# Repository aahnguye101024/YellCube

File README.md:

# YellCube
This device is intended to connect stream audio and flash lights representative of the audio. This device streams songs that are uploaded to another repo (https://github.com/aahnguye101024/ESP32Audio). This project was also a way for me to test out the 3D printer I just bought in a fun way. With an ESP32 pico d4 with an antenna, onboard leds, a dedicated SK6812 LED board, an audio amplifier, an onboard lipo with supported charging and uploading straight to the pico D4, this board can be easily programmed and adapted to any of your speaker and lights project needs.

# Main Board

# Lights Board

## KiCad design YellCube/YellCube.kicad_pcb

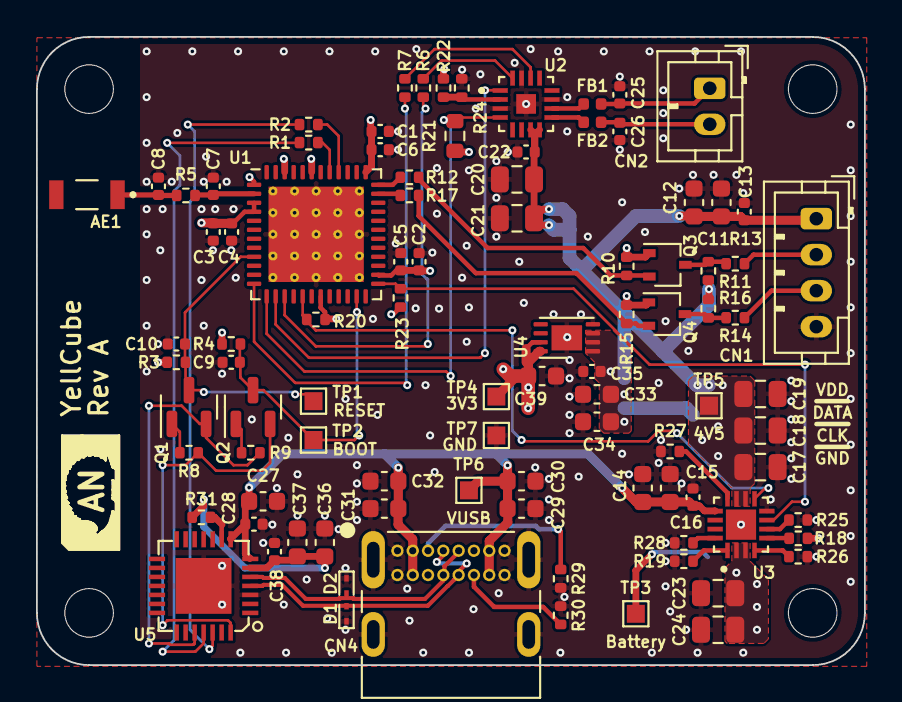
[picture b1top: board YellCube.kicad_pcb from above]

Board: 4 copper layers, 46.0 x 34.9 mm, 99 parts (1 on the bottom side), 50 nets.

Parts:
AE1: AMCA31-2R450G-S1F-T3; ANT_AMCA31-2R450G-S1F-T3
C1, C2, C3, C10: 1uF; C_0402_1005Metric
C4, C5, C6, C9, C13, C16, C22, C28, C35, C38: 0.1uF; C_0402_1005Metric
C7: 2.7pF; C_0402_1005Metric
C8: 2pF; C_0402_1005Metric
C11, C12, C33, C34, C39: 4.7uF; C_0603_1608Metric
C14, C15, C27, C29, C30, C31, C32, C36, C37: 2.2uF; C_0603_1608Metric
C17, C18, C19, C20, C21, C23, C24: 10uF; C_0805_2012Metric
C25, C26: 220pF; C_0402_1005Metric
CN1: B4B-PH-K-S(LF)(SN); JST_PH_B4B-PH-K_1x04_P2.00mm_Vertical
CN2: B2B-PH-K-S(LF)(SN); JST_PH_B2B-PH-K_1x02_P2.00mm_Vertical
CN3: S2B-PH-SM4-TB(LF)(SN); JST_S2B-PH-SM4-TB(LF)(SN)
CN4: 2137160001
D1, D2: ESD7951ST5G; D_SOD-923
FB1, FB2: BLM15PX601SN1D; L_0402_1005Metric
H1, H2, H3, H4: MountingHole; MountingHole_2.7mm_M2.5_ISO14580
Q1, Q2: MMBT3904; SOT-23
Q3, Q4: BSS138W-7-F; SOT-323_SC-70
R1, R2, R5, R12, R13, R14, R17: 0; R_0402_1005Metric
R3, R8, R9, R10, R11, R15, R16, R18, R19, R20, R23, R25, R26, R31: 10k; R_0402_1005Metric
R4, R28: 4.7k; R_0402_1005Metric
R6, R7: 33; R_0402_1005Metric
R21: 680k; R_0603_1608Metric
R22, R24: 100k; R_0402_1005Metric
R27: 3.09k; R_0402_1005Metric
R29, R30: 5.1k; R_0402_1005Metric
TP1: RESET; CurrentTestPoint
TP2: BOOT; CurrentTestPoint
TP3: Battery; CurrentTestPoint
TP4: 3V3; CurrentTestPoint
TP5: 4V5; CurrentTestPoint
TP6: VUSB; CurrentTestPoint
TP7: GND; CurrentTestPoint
U1: ESP32-PICO-D4; QFN-48-1EP_7x7mm_P0.5mm_EP5.3x5.3mm_ThermalVias
U2: MAX98357AETE+T; QFN50P300X300X80-17N
U3: BQ24232HARGTR; QFN50P300X300X100-17N
U4: MCP1725T-3302E/MC; MCP1725T-3302E
U5: CP2102-GMR; QFN28G_0.5-5X5MM

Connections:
+3V3: C1.1, C2.1, C3.1, C4.1, C5.1, C6.1, C39.1, Q3.1 (G), Q4.1 (G), R3.1, R4.1, R10.1, R15.1, R18.1, R20.2, R21.1, R22.2, R23.2, TP4.1, U1.1 (VDDA), U1.3 (VDDA3P3), U1.4 (VDDA3P3), U1.19 (VDD3P3_RTC), U1.26 (VDD_SDIO), U1.37 (VDD3P3_CPU), U1.43 (VDDA), U1.46 (VDDA), U4.7 (SENSE), U4.8 (VOUT)
+BATT: C23.1, C24.1, CN3.2, TP3.1, U3.2 (BAT), U3.3 (BAT)
/AUDIO_BCLK: R6.2, U2.16 (BCLK)
/AUDIO_DIN: U1.14 (IO25), U2.1 (DIN)
/AUDIO_LRCLK: R7.2, U2.14 (LRCLK)
/AUDIO_OUTN: C25.1, CN2.1, FB1.2
/AUDIO_OUTP: C26.1, CN2.2, FB2.2
/AUDIO_SD: R21.2, U1.13 (IO33), U2.4 (~SD_MODE)
/DTR: Q2.2 (E), R8.2, U5.28 (DTR)
/ESP_EN: C10.1, Q1.3 (C), R3.2, TP1.1, U1.9 (EN)
/IO0: C9.1, Q2.3 (C), R4.2, TP2.1, U1.23 (IO0)
/LED_CLK: R17.1, U1.35 (IO18)
/LED_CON_CLK: CN1.3, R14.2
/LED_CON_DATA: CN1.2, R13.2
/LED_DATA: R12.1, U1.36 (IO23)
/LNA_IN: C7.1, R5.2, U1.2 (LNA_IN)
/LNA_OUT: AE1.1 (A), C8.1, R5.1
/RTS: Q1.2 (E), R9.2, U5.24 (RTS)
/UART_RX: R1.1, U5.25 (RXD)
/UART_TX: R2.1, U5.26 (TXD)
/USB_N: CN4.A7 (D-), CN4.B7 (D-), D2.2 (A2), U5.5 (D-)
/USB_P: CN4.A6 (D+), CN4.B6 (D+), D1.2 (A2), U5.4 (D+)
/nCHG: R20.1, U1.17 (IO14), U3.9 (~CHG)
/nPGOOD: R23.1, U1.25 (IO16), U3.7 (~PGOOD)
GND: C1.2, C2.2, C3.2, C4.2, C5.2, C6.2, C7.2, C8.2, C9.2, C10.2, C11.2, C12.2, C13.2, C14.2, C15.2, C16.2, C17.2, C18.2, C19.2, C20.2, C21.2, C22.2, C23.2, C24.2, C25.2, C26.2, C27.2, C28.2, C29.2, C30.2, C31.2, C32.2, C33.2, C34.2, C35.2, C36.2, C37.2, C38.2, C39.2, CN1.4, CN3.1, CN3.MP (MountPin), CN4.A1 (GND), CN4.A12 (GND), CN4.B1 (GND), CN4.B12 (GND), CN4.S (SHIELD), D1.1 (A1), D2.1 (A1), R19.2, R24.1, R25.2, R26.2, R27.2, R28.2, R29.2, R30.2, TP7.1, U1.49 (GND), U2.3 (GND), U2.11 (GND), U2.15 (GND), U2.17 (EP), U3.8 (VSS), U3.17 (THERMALPAD), U4.4 (GND), U4.9 (PAD), U5.3 (GND), U5.29 (GND)
unnamed: C36.1, C37.1, C38.1, R31.1, U5.6 (VDD)
unnamed: CN4.A5 (CC1), R29.1
unnamed: CN4.B5 (CC2), R30.1
unnamed: FB1.1, U2.10 (OUTN)
unnamed: FB2.1, U2.9 (OUTP)
unnamed: Q1.1 (B), R8.1
unnamed: Q2.1 (B), R9.1
unnamed: Q3.2 (S), R10.2, R12.2
unnamed: Q3.3 (D), R11.2, R13.1
unnamed: Q4.2 (S), R15.2, R17.2
unnamed: Q4.3 (D), R14.1, R16.2
unnamed: R1.2, U1.41 (U0TXD)
unnamed: R2.2, U1.40 (U0RXD)
unnamed: R6.1, U1.15 (IO26)
unnamed: R7.1, U1.12 (IO32)
unnamed: R18.2, U3.5 (EN2)
unnamed: R19.1, U3.1 (TS)
unnamed: R22.1, R24.2, U2.2 (GAIN_SLOT)
unnamed: R25.1, U3.6 (EN1)
unnamed: R26.1, U3.4 (~CE)
unnamed: R27.1, U3.12 (ILIM)
unnamed: R28.1, U3.16 (ISET)
unnamed: R31.2, U5.9 (~RST)
VBUS: C14.1, C15.1, C16.1, C27.1, C28.1, C29.1, C30.1, C31.1, C32.1, CN4.A4 (VBUS), CN4.A9 (VBUS), CN4.B4 (VBUS), CN4.B9 (VBUS), TP6.1, U3.13 (IN), U5.7 (REGIN), U5.8 (VBUS)
VDD: C11.1, C12.1, C13.1, C17.1, C18.1, C19.1, C20.1, C21.1, C22.1, C33.1, C34.1, C35.1, CN1.1, R11.1, R16.1, TP5.1, U2.7 (VDD), U2.8 (VDD), U3.10 (OUT), U3.11 (OUT), U4.1 (VIN), U4.2 (VIN), U4.3 (~SHDN)

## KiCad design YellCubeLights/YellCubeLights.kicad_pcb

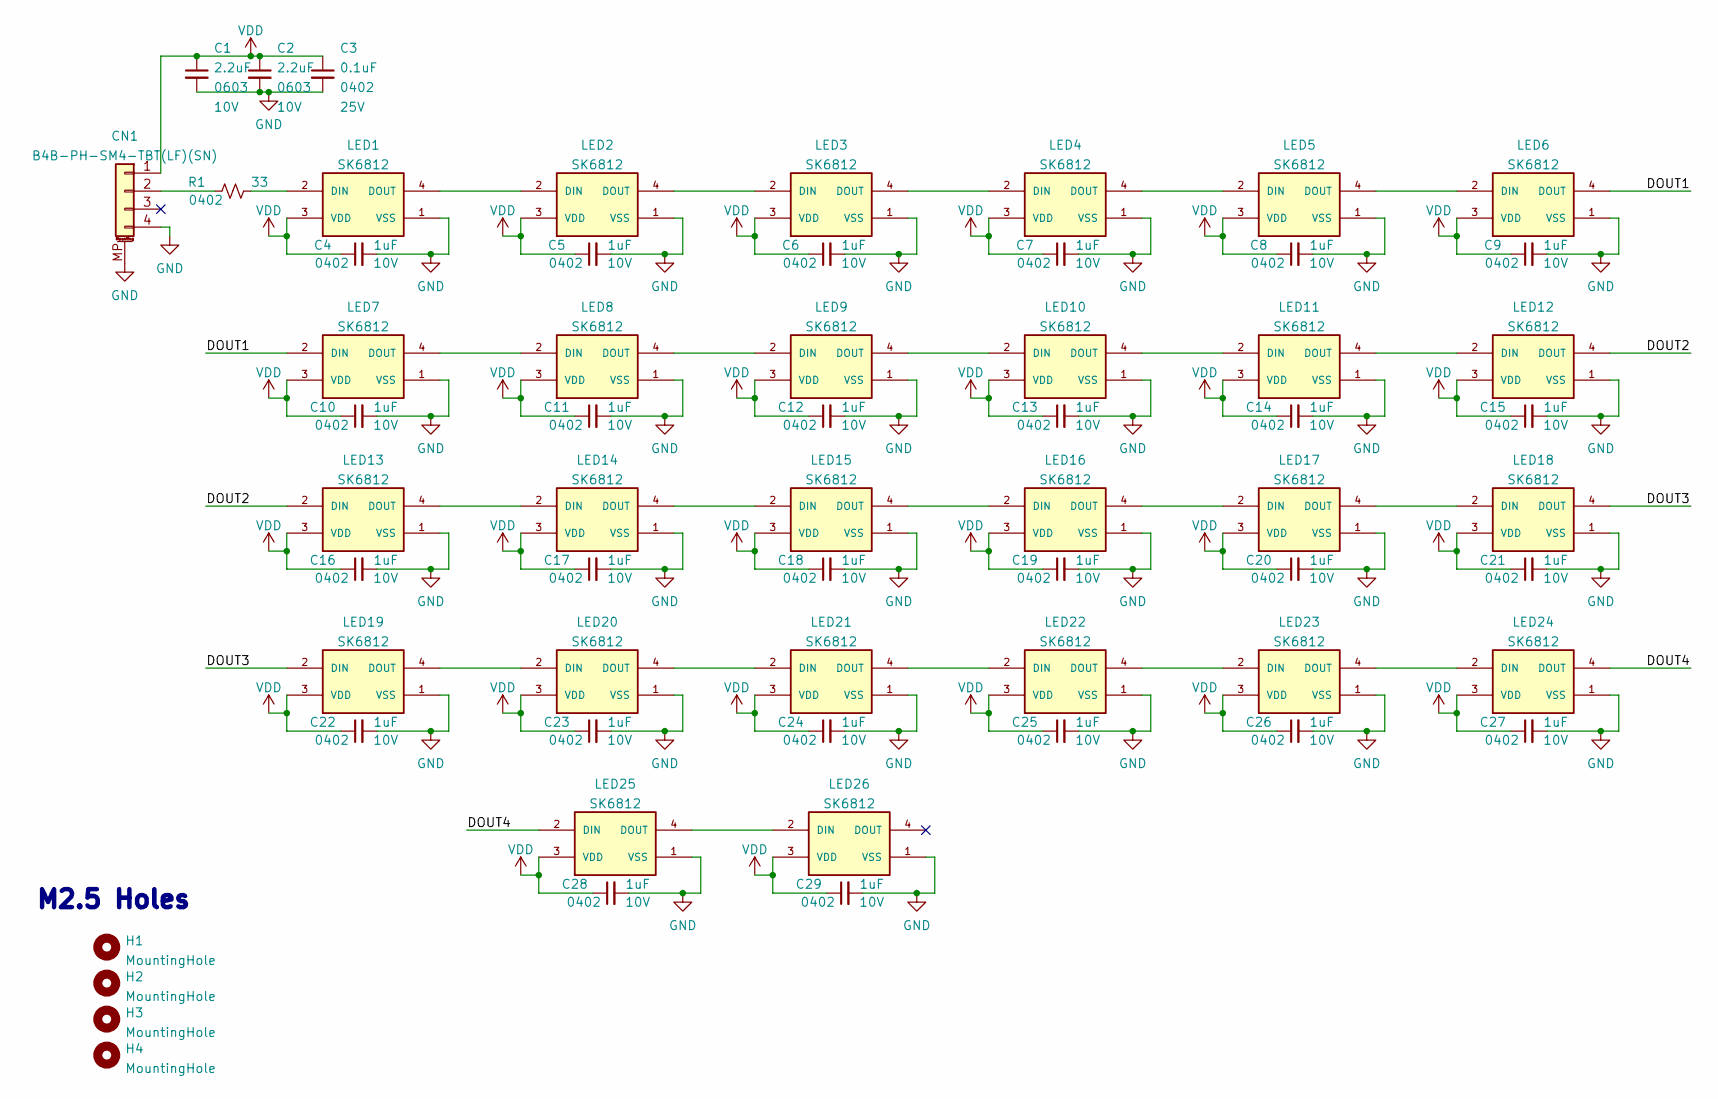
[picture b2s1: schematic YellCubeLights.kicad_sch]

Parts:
C1, C2: 2.2uF; C_0603_1608Metric; Voltage 10V; Part Number 1276-1085-1-ND
C3: 0.1uF; C_0402_1005Metric; Voltage 25V; Part Number 1276-1043-1-ND
C4, C5, C6, C7, C8, C9, C10, C11, C12, C13, C14, C15, C16, C17, C18, C19, C20, C21, C22, C23, C24, C25, C26, C27, C28, C29: 1uF; C_0402_1005Metric; Voltage 10V; Part Number 1276-1076-1-ND
CN1: B4B-PH-SM4-TBT(LF)(SN); Part Number 455-2873-1-ND
H1, H2, H3, H4: MountingHole; MountingHole_2.7mm_M2.5_ISO14580
LED1, LED2, LED3, LED4, LED5, LED6, LED7, LED8, LED9, LED10, LED11, LED12, LED13, LED14, LED15, LED16, LED17, LED18, LED19, LED20, LED21, LED22, LED23, LED24, LED25, LED26: SK6812; Part Number N/A
R1: 33; R_0402_1005Metric; Part Number 311-33.0LRCT-ND

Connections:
/DOUT1: LED6.4 (DOUT), LED7.2 (DIN)
/DOUT2: LED12.4 (DOUT), LED13.2 (DIN)
/DOUT3: LED18.4 (DOUT), LED19.2 (DIN)
/DOUT4: LED24.4 (DOUT), LED25.2 (DIN)
GND: C1.2, C2.2, C3.2, C4.2, C5.2, C6.2, C7.2, C8.2, C9.2, C10.2, C11.2, C12.2, C13.2, C14.2, C15.2, C16.2, C17.2, C18.2, C19.2, C20.2, C21.2, C22.2, C23.2, C24.2, C25.2, C26.2, C27.2, C28.2, C29.2, CN1.4, CN1.MP (MountPin), LED1.1 (VSS), LED2.1 (VSS), LED3.1 (VSS), LED4.1 (VSS), LED5.1 (VSS), LED6.1 (VSS), LED7.1 (VSS), LED8.1 (VSS), LED9.1 (VSS), LED10.1 (VSS), LED11.1 (VSS), LED12.1 (VSS), LED13.1 (VSS), LED14.1 (VSS), LED15.1 (VSS), LED16.1 (VSS), LED17.1 (VSS), LED18.1 (VSS), LED19.1 (VSS), LED20.1 (VSS), LED21.1 (VSS), LED22.1 (VSS), LED23.1 (VSS), LED24.1 (VSS), LED25.1 (VSS), LED26.1 (VSS)
unnamed: LED1.2 (DIN), R1.2
unnamed: LED1.4 (DOUT), LED2.2 (DIN)
unnamed: LED2.4 (DOUT), LED3.2 (DIN)
unnamed: LED3.4 (DOUT), LED4.2 (DIN)
unnamed: LED4.4 (DOUT), LED5.2 (DIN)
unnamed: LED5.4 (DOUT), LED6.2 (DIN)
unnamed: LED7.4 (DOUT), LED8.2 (DIN)
unnamed: LED8.4 (DOUT), LED9.2 (DIN)
unnamed: LED9.4 (DOUT), LED10.2 (DIN)
unnamed: LED10.4 (DOUT), LED11.2 (DIN)
unnamed: LED11.4 (DOUT), LED12.2 (DIN)
unnamed: LED13.4 (DOUT), LED14.2 (DIN)
unnamed: LED14.4 (DOUT), LED15.2 (DIN)
unnamed: LED15.4 (DOUT), LED16.2 (DIN)
unnamed: LED16.4 (DOUT), LED17.2 (DIN)
unnamed: LED17.4 (DOUT), LED18.2 (DIN)
unnamed: LED19.4 (DOUT), LED20.2 (DIN)
unnamed: LED20.4 (DOUT), LED21.2 (DIN)
unnamed: LED21.4 (DOUT), LED22.2 (DIN)
unnamed: LED22.4 (DOUT), LED23.2 (DIN)
unnamed: LED23.4 (DOUT), LED24.2 (DIN)
unnamed: LED25.4 (DOUT), LED26.2 (DIN)
unnamed: CN1.2, R1.1
VDD: C1.1, C2.1, C3.1, C4.1, C5.1, C6.1, C7.1, C8.1, C9.1, C10.1, C11.1, C12.1, C13.1, C14.1, C15.1, C16.1, C17.1, C18.1, C19.1, C20.1, C21.1, C22.1, C23.1, C24.1, C25.1, C26.1, C27.1, C28.1, C29.1, CN1.1, LED1.3 (VDD), LED2.3 (VDD), LED3.3 (VDD), LED4.3 (VDD), LED5.3 (VDD), LED6.3 (VDD), LED7.3 (VDD), LED8.3 (VDD), LED9.3 (VDD), LED10.3 (VDD), LED11.3 (VDD), LED12.3 (VDD), LED13.3 (VDD), LED14.3 (VDD), LED15.3 (VDD), LED16.3 (VDD), LED17.3 (VDD), LED18.3 (VDD), LED19.3 (VDD), LED20.3 (VDD), LED21.3 (VDD), LED22.3 (VDD), LED23.3 (VDD), LED24.3 (VDD), LED25.3 (VDD), LED26.3 (VDD)

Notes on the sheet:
M2.5 Holes

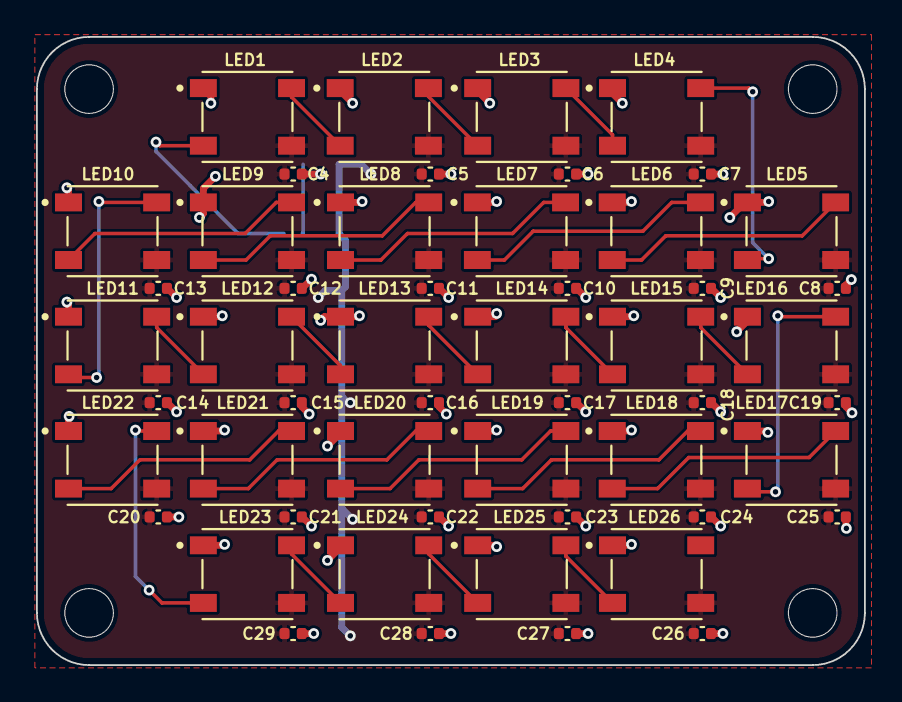
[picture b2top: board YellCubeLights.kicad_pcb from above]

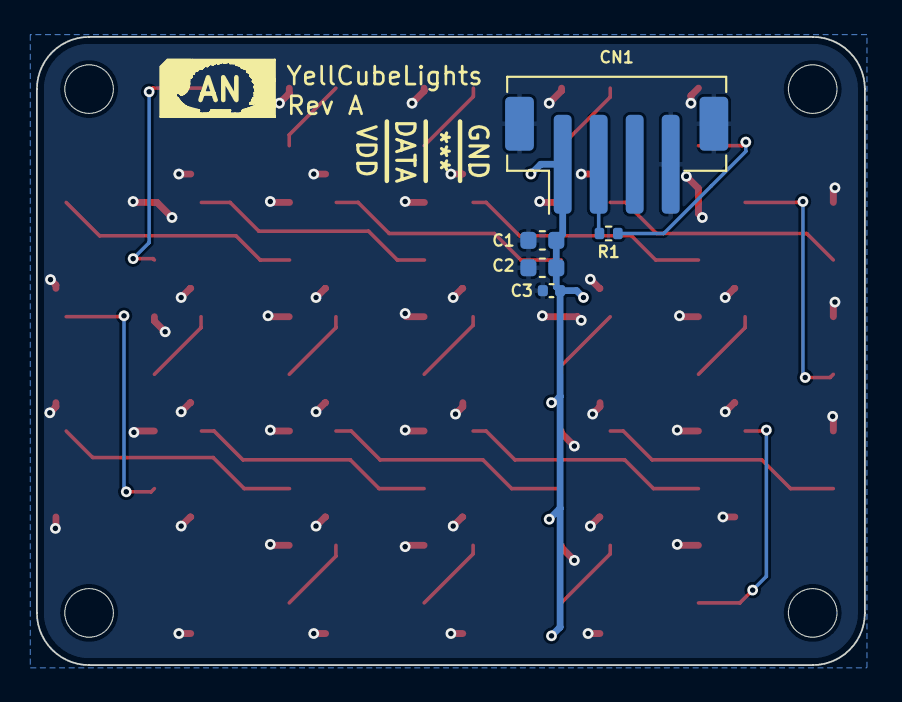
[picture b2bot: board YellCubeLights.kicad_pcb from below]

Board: 2 copper layers, 46.0 x 34.9 mm, 61 parts (5 on the bottom side), 29 nets.

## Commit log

2024-01-31 Initial Push
2024-01-31 Updated read me
